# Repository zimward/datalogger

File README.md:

4-20mA dual channel Datalogger for long term averaging of in-field bus systems

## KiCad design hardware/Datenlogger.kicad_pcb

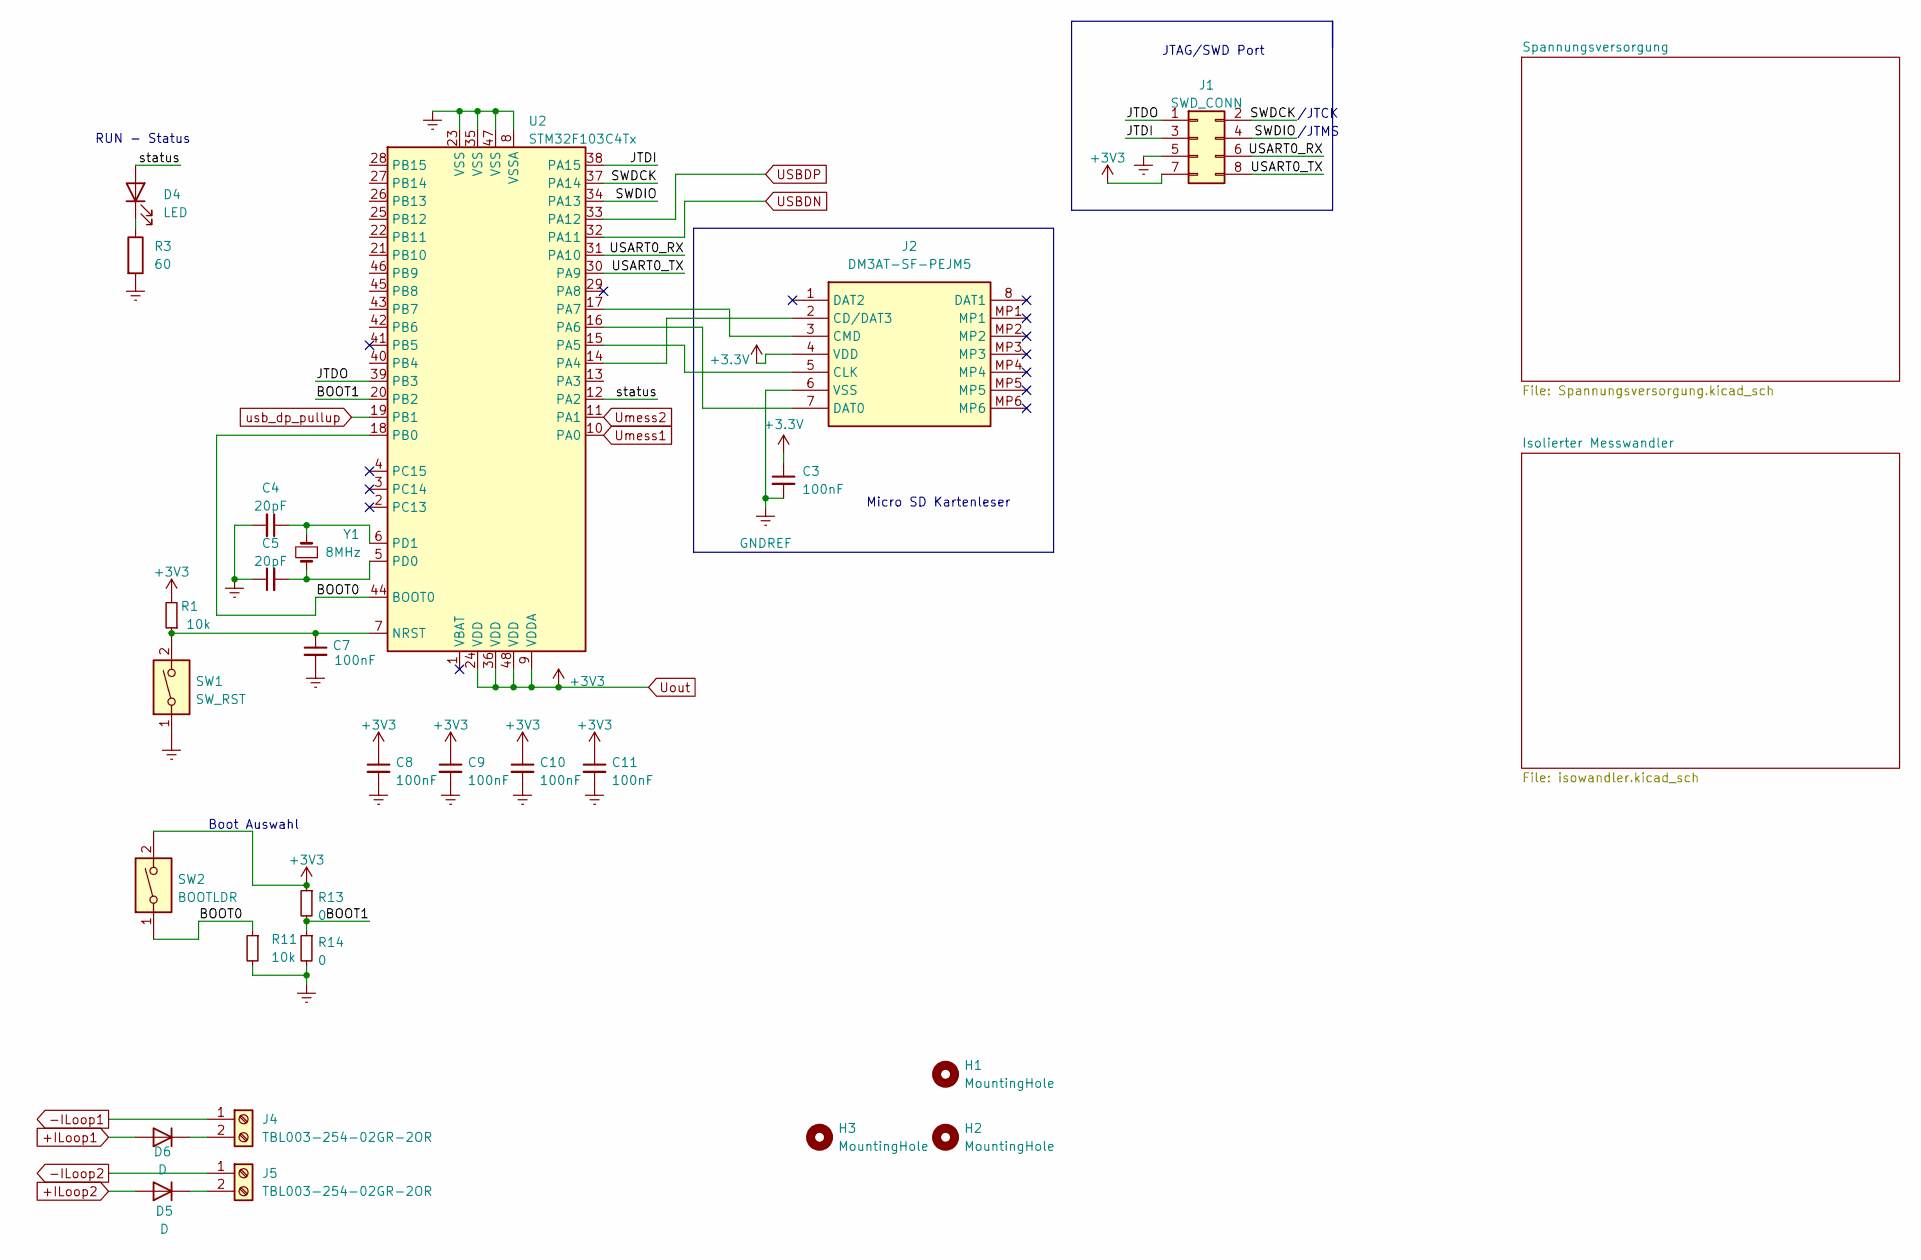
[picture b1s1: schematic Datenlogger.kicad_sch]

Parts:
C3, C7, C8, C9, C10, C11: 100nF; C_0805_2012Metric_Pad1.18x1.45mm_HandSolder
C4, C5: 20pF; C_0805_2012Metric_Pad1.18x1.45mm_HandSolder
D4: LED; LED_0805_2012Metric_Pad1.15x1.40mm_HandSolder
D5, D6: D; D_SOD-123
H1, H2, H3: MountingHole; MountingHole_3.2mm_M3_DIN965
J1: SWD_CONN; PinHeader_2x04_P2.54mm_Vertical
J2: DM3AT-SF-PEJM5; DM3ATSFPEJM5; Mouser Part Number 798-DM3AT-SF-PEJM5
J4, J5: TBL003-254-02GR-2OR; SHDR4W70P508X254_2X2_768X1380X1275P
R1, R11: 10k; R_0805_2012Metric_Pad1.20x1.40mm_HandSolder
R3: 60; R_0805_2012Metric_Pad1.20x1.40mm_HandSolder
R13, R14: 0; R_0805_2012Metric_Pad1.20x1.40mm_HandSolder
SW1: SW_RST; SW_DIP_SPSTx01_Slide_6.7x4.1mm_W7.62mm_P2.54mm_LowProfile
SW2: BOOTLDR; SW_DIP_SPSTx01_Slide_6.7x4.1mm_W7.62mm_P2.54mm_LowProfile
U2: STM32F103C4Tx; LQFP-48_7x7mm_P0.5mm
Y1: 8MHz; Crystal_SMD_HC49-SD

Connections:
+ILoop1: D6.2 (A); also elsewhere on the board
+ILoop2: D5.2 (A); also elsewhere on the board
-ILoop1: J4.1; also elsewhere on the board
-ILoop2: J5.1; also elsewhere on the board
/BOOT0: R11.1, SW2.1, U2.18 (PB0), U2.44 (BOOT0)
/BOOT1: R13.2, R14.1, U2.20 (PB2)
/JTDI: J1.3, U2.38 (PA15)
/JTDO: J1.1, U2.39 (PB3)
/SWDCK: J1.2, U2.37 (PA14)
/SWDIO: J1.4, U2.34 (PA13)
/USART0_RX: J1.6, U2.31 (PA10)
/USART0_TX: J1.8, U2.30 (PA9)
/status: D4.2 (A), U2.12 (PA2)
GNDREF: C3.2, C4.2, C5.1, C7.2, C8.2, C9.2, C10.2, C11.2, J1.5, J2.6 (VSS), R3.2, R11.2, R14.2, SW1.1, U2.8 (VSSA), U2.23 (VSS), U2.35 (VSS), U2.47 (VSS); also elsewhere on the board
unnamed: D4.1 (K), R3.1
unnamed: D5.1 (K), J5.2
unnamed: D6.1 (K), J4.2
unnamed: J2.2 (CD/DAT3), U2.14 (PA4)
unnamed: J2.5 (CLK), U2.15 (PA5)
unnamed: J2.3 (CMD), U2.17 (PA7)
unnamed: J2.7 (DAT0), U2.16 (PA6)
unnamed: C7.1, R1.1, SW1.2, U2.7 (NRST)
unnamed: C5.2, U2.5 (PD0), Y1.1
unnamed: C4.1, U2.6 (PD1), Y1.2
USBDN: U2.32 (PA11); also elsewhere on the board
USBDP: U2.33 (PA12); also elsewhere on the board
Umess1: U2.10 (PA0); also elsewhere on the board
Umess2: U2.11 (PA1); also elsewhere on the board
Uout: C3.1, C8.1, C9.1, C10.1, C11.1, J1.7, J2.4 (VDD), R1.2, R13.1, SW2.2, U2.9 (VDDA), U2.24 (VDD), U2.36 (VDD), U2.48 (VDD); also elsewhere on the board
usb_dp_pullup: U2.19 (PB1); also elsewhere on the board

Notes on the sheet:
JTAG/SWD Port
Micro SD Kartenleser
/JTMS
/JTCK
Boot Auswahl
RUN - Status

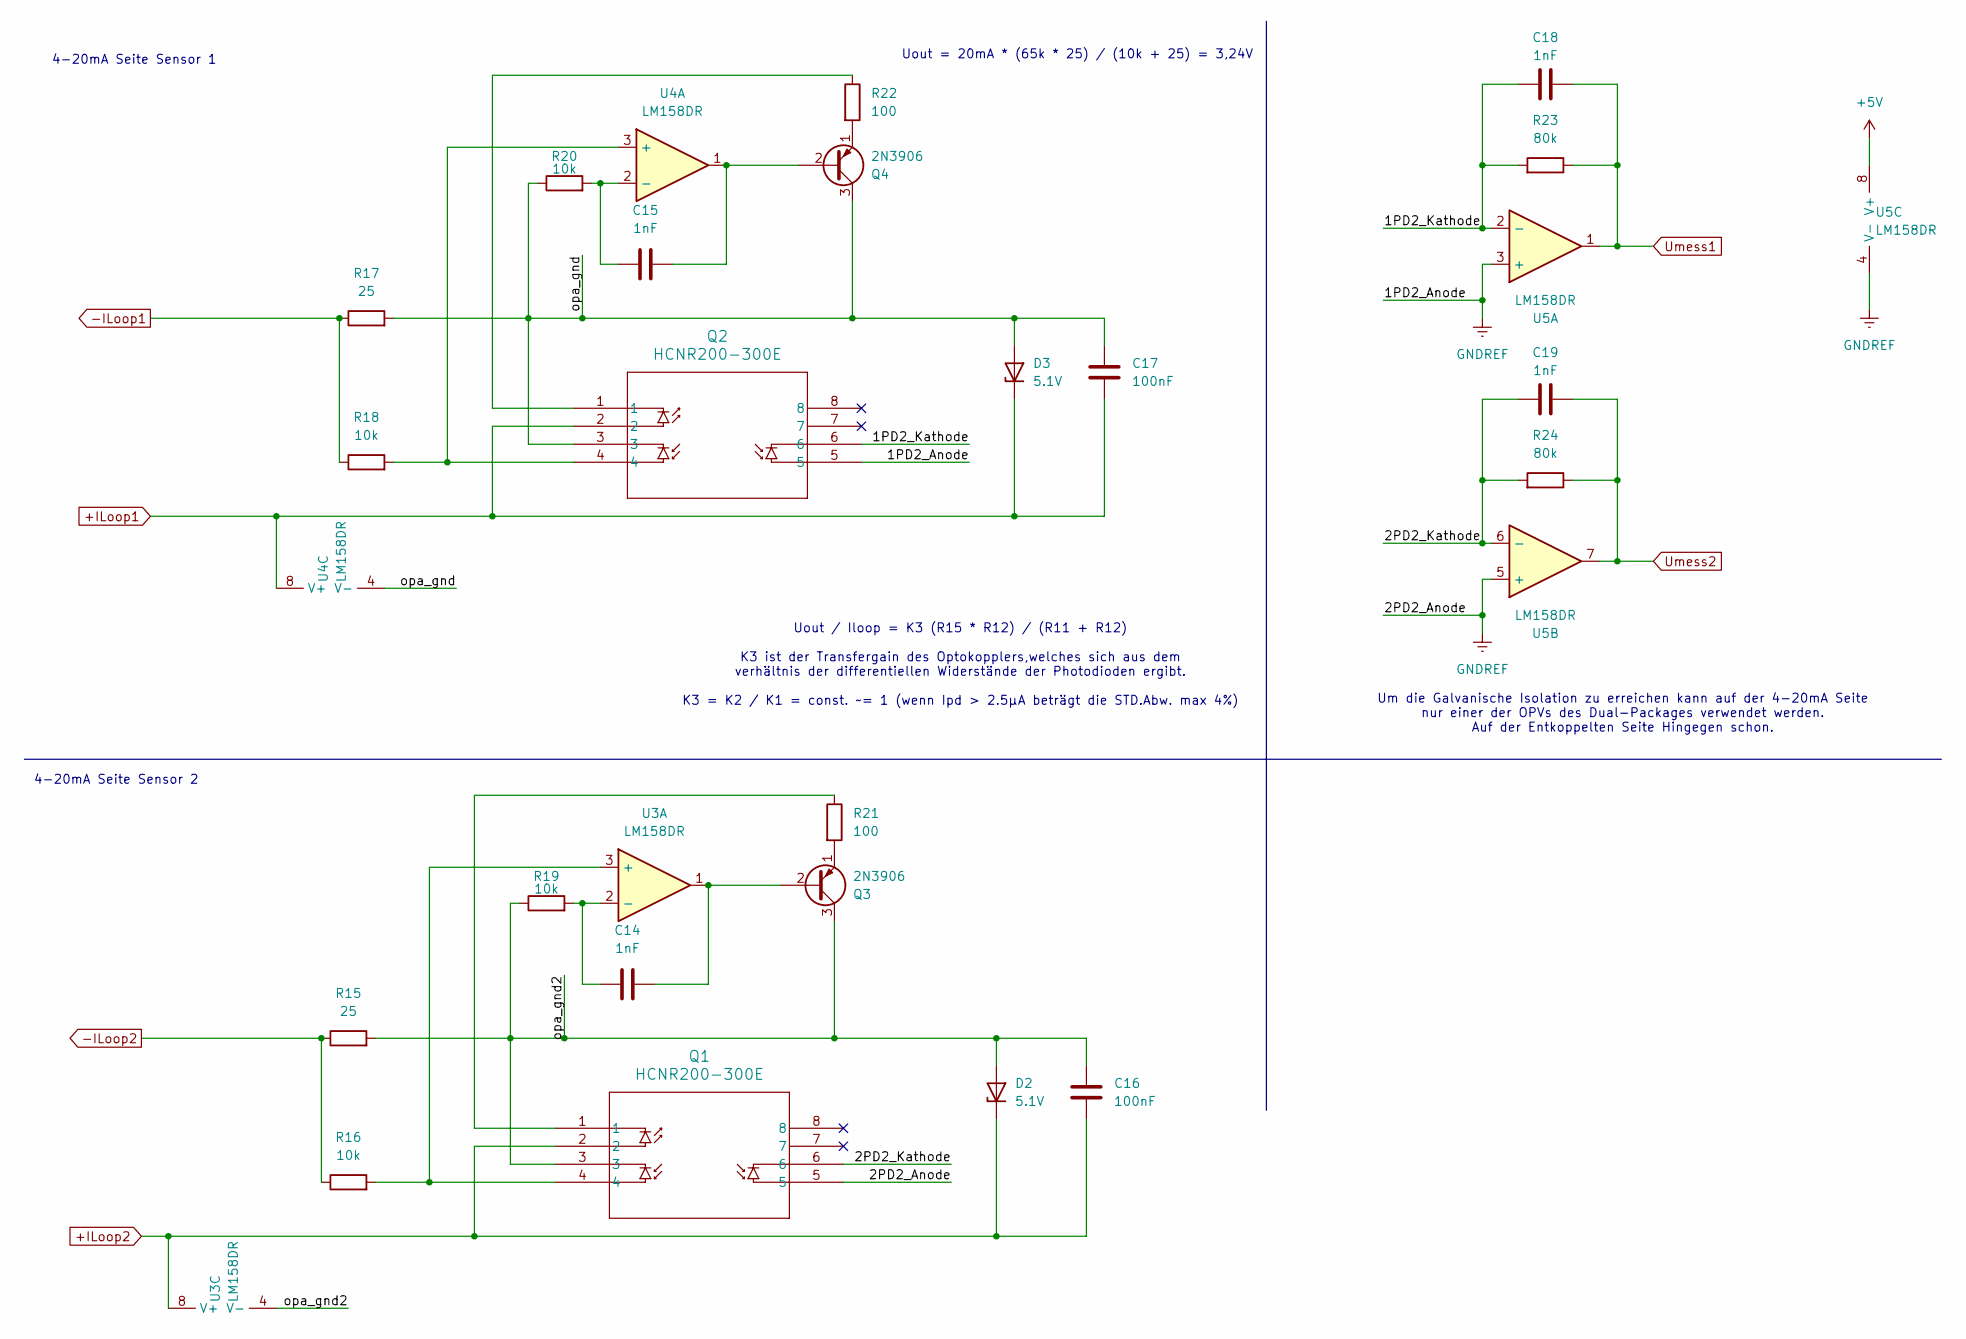
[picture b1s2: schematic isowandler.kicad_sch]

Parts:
C14, C15, C18, C19: 1nF; C_0805_2012Metric_Pad1.18x1.45mm_HandSolder
C16, C17: 100nF; C_0805_2012Metric_Pad1.18x1.45mm_HandSolder
D2, D3: 5.1V; D_SOD-123
Q1, Q2: HCNR200-300E
Q3, Q4: 2N3906; TO-92_Inline_Wide
R15, R17: 25; R_0805_2012Metric_Pad1.20x1.40mm_HandSolder
R16, R18, R19, R20: 10k; R_0805_2012Metric_Pad1.20x1.40mm_HandSolder
R21, R22: 100; R_0805_2012Metric_Pad1.20x1.40mm_HandSolder
R23, R24: 80k; R_0805_2012Metric_Pad1.20x1.40mm_HandSolder
U3, U4, U5: LM158DR; SOP-8_3.76x4.96mm_P1.27mm

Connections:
+5V: U5.8 (V+)
+ILoop1: C17.2, D3.1 (K), Q2.2, U4.8 (V+); also elsewhere on the board
+ILoop2: C16.2, D2.1 (K), Q1.2, U3.8 (V+); also elsewhere on the board
-ILoop1: R17.1, R18.1; also elsewhere on the board
-ILoop2: R15.1, R16.1; also elsewhere on the board
/Isolierter Messwandler/1PD2_Kathode: C18.1, Q2.6, R23.2, U5.2 (-)
/Isolierter Messwandler/2PD2_Kathode: C19.1, Q1.6, R24.2, U5.6 (-)
/Isolierter Messwandler/opa_gnd: C17.1, D3.2 (A), Q2.3, Q4.3 (C), R17.2, R20.1, U4.4 (V-)
/Isolierter Messwandler/opa_gnd2: C16.1, D2.2 (A), Q1.3, Q3.3 (C), R15.2, R19.1, U3.4 (V-)
GNDREF: Q1.5, Q2.5, U5.3 (+), U5.4 (V-), U5.5 (+); also elsewhere on the board
unnamed: Q1.1, R21.1
unnamed: Q2.1, R22.1
unnamed: C14.2, Q3.2 (B), U3.1
unnamed: Q3.1 (E), R21.2
unnamed: C15.2, Q4.2 (B), U4.1
unnamed: Q4.1 (E), R22.2
unnamed: Q1.4, R16.2, U3.3 (+)
unnamed: C14.1, R19.2, U3.2 (-)
unnamed: Q2.4, R18.2, U4.3 (+)
unnamed: C15.1, R20.2, U4.2 (-)
Umess1: C18.2, R23.1, U5.1; also elsewhere on the board
Umess2: C19.2, R24.1, U5.7; also elsewhere on the board

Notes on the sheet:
Um die Galvanische Isolation zu erreichen kann auf der 4-20mA Seite nur einer der OPVs des Dual-Packages verwendet werden. Auf der Entkoppelten Seite Hingegen schon.
Uout = 20mA * (65k * 25) / (10k + 25) = 3,24V
4-20mA Seite Sensor 1
Uout / Iloop = K3 (R15 * R12) / (R11 + R12) K3 ist der Transfergain des Optokopplers,welches sich aus dem verhältnis der differentiellen Widerstände der Photodioden ergibt. K3 = K2 / K1 = const. ~= 1 (wenn Ipd > 2.5µA beträgt die STD.Abw. max 4%)
4-20mA Seite Sensor 2

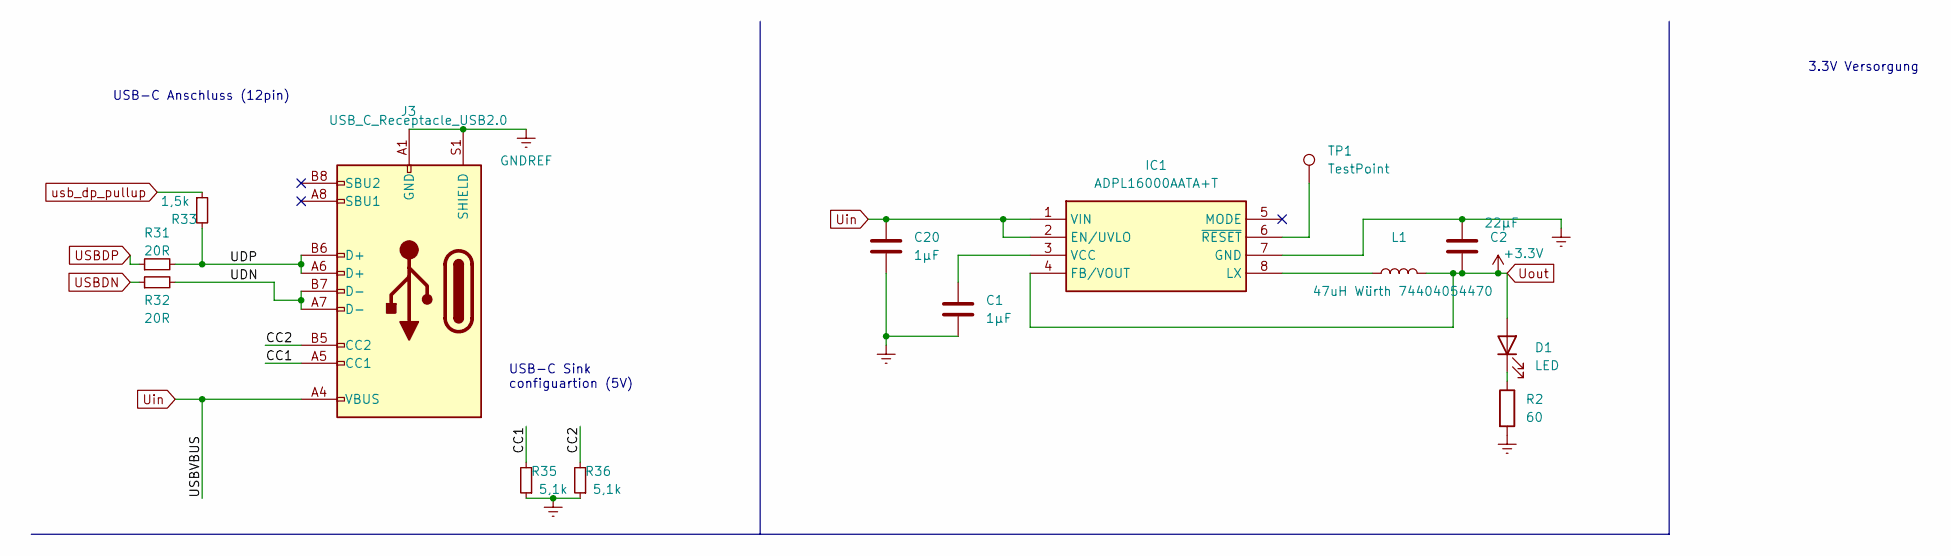
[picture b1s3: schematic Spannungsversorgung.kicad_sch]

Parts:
C1: 1µF; C_0805_2012Metric_Pad1.18x1.45mm_HandSolder
C2: 22µF; C_0805_2012Metric_Pad1.18x1.45mm_HandSolder
C20: 1µF; C_0805_2012Metric
D1: LED; LED_0805_2012Metric_Pad1.15x1.40mm_HandSolder
IC1: ADPL16000AATA+T; ADPL16000AATAT; Mouser Part Number 700-ADPL16000AATA+T
J3: USB_C_Receptacle_USB2.0; USB_C_Receptacle_Palconn_UTC16-G
L1: 47uH Würth 74404054470; 74404054470
R2: 60; R_0805_2012Metric_Pad1.20x1.40mm_HandSolder
R31, R32: 20R; R_0805_2012Metric_Pad1.20x1.40mm_HandSolder
R33: 1,5k; R_0805_2012Metric_Pad1.20x1.40mm_HandSolder
R35, R36: 5,1k; R_0805_2012Metric_Pad1.20x1.40mm_HandSolder
TP1: TestPoint; TestPoint_Pad_1.5x1.5mm

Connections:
/Spannungsversorgung/CC1: J3.A5 (CC1), R35.2
/Spannungsversorgung/CC2: J3.B5 (CC2), R36.2
/Spannungsversorgung/UDN: J3.A7 (D-), J3.B7 (D-), R32.2
/Spannungsversorgung/UDP: J3.A6 (D+), J3.B6 (D+), R31.2, R33.2
GNDREF: C1.2, C2.1, C20.2, IC1.7 (GND), J3.A1 (GND), J3.A12 (GND), J3.B1 (GND), J3.B12 (GND), J3.S1 (SHIELD), R2.2, R35.1, R36.1; also elsewhere on the board
unnamed: D1.1 (K), R2.1
unnamed: IC1.8 (LX), L1.1
unnamed: C1.1, IC1.3 (VCC)
unnamed: IC1.6 (~RESET), TP1.1
USBDN: R32.1; also elsewhere on the board
USBDP: R31.1; also elsewhere on the board
Uin: C20.1, IC1.1 (VIN), IC1.2 (EN/UVLO), J3.A4 (VBUS), J3.A9 (VBUS), J3.B4 (VBUS), J3.B9 (VBUS)
Uout: C2.2, D1.2 (A), IC1.4 (FB/VOUT), L1.2; also elsewhere on the board
usb_dp_pullup: R33.1; also elsewhere on the board

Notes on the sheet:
USB-C Sink configuartion (5V)
3.3V Versorgung
USB-C Anschluss (12pin)

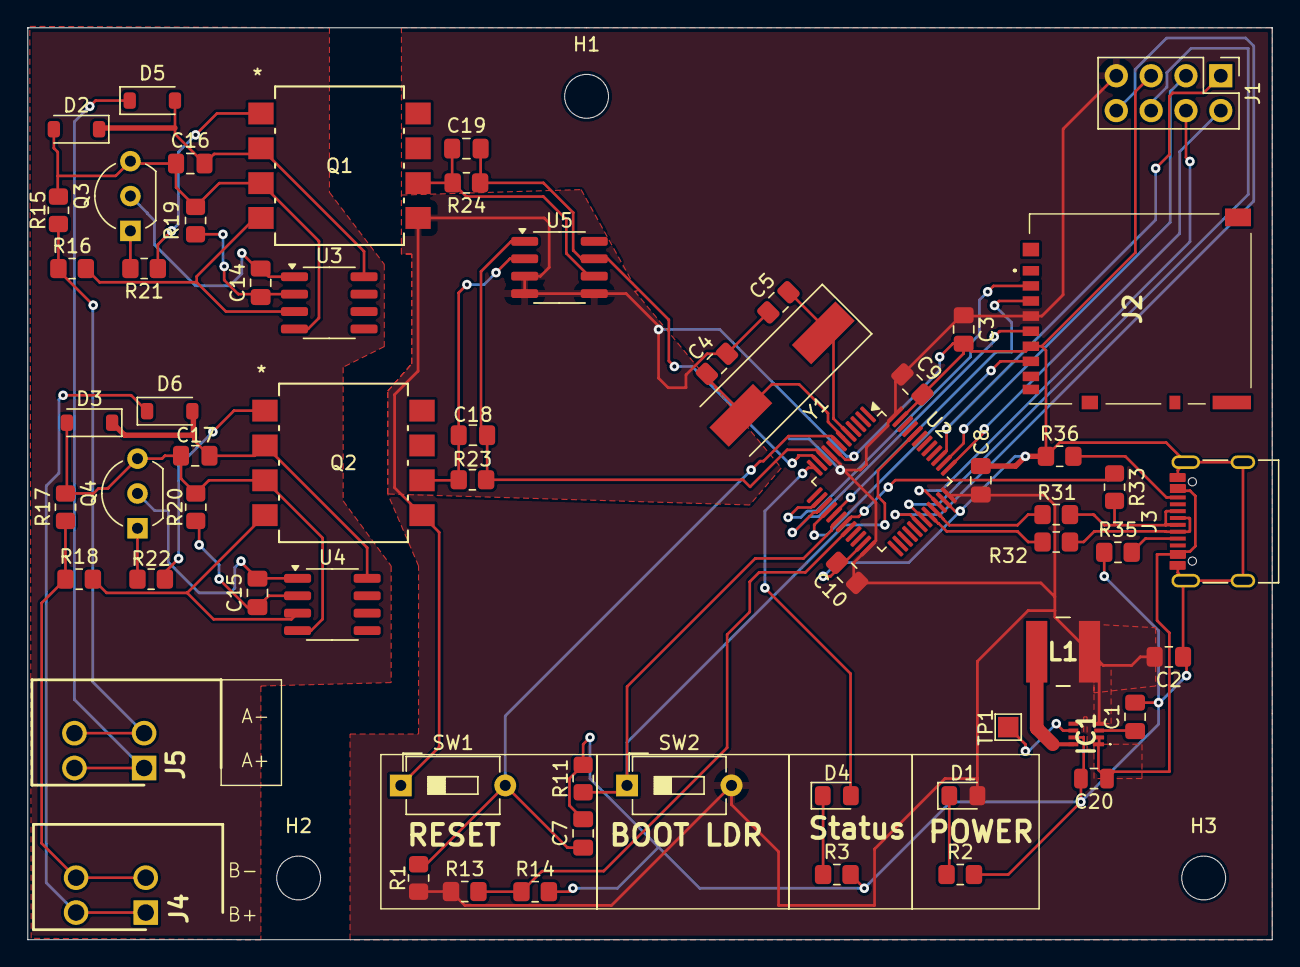
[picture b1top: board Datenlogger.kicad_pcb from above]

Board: 2 copper layers, 90.8 x 66.5 mm, 66 parts (1 on the bottom side), 53 nets.

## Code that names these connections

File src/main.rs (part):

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use sdcard::{config_error, sderror, FakeTimeSource};
use stm32f1xx_hal::adc::{Adc, SampleTime, SetChannels};
use stm32f1xx_hal::dma::Half;
use stm32f1xx_hal::gpio::{Analog, PA0, PA1};
use stm32f1xx_hal::pac::{ADC1, NVIC, TIM3};

use stm32f1xx_hal::spi::Spi;
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/*
#######################
pin  funktion
PB1  usb dp pin pullup
PA0  messkanal B
PA1  messkanal A
PA2  status LED
PB0 start/stop -- in dokumentation nach remap möglichkeit schauen.

#######################
*/
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
    //ADC dma config
    let mut adc = {
        struct AdcPins(PA0<Analog>, PA1<Analog>);
        impl SetChannels<AdcPins> for Adc<ADC1> {
            fn set_sequence(&mut self) {
                //first channel A then B, but doesn't really matter
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            }
        }

        let channelB = gpioa.pa0.into_analog(&mut gpioa.crl);
        let channelA = gpioa.pa1.into_analog(&mut gpioa.crl);

        let mut adc = Adc::adc1(dp.ADC1, clocks);
        //slowest sampling time should be sufficient
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    let mut gpiob = dp.GPIOB.split();
    let spi = {
        let pins = (
            gpioa.pa5.into_alternate_push_pull(&mut gpioa.crl),
            gpioa.pa6.into_pull_up_input(&mut gpioa.crl),
            gpioa.pa7.into_alternate_push_pull(&mut gpioa.crl),
        );
        let spi_mode = Mode {
            polarity: embedded_hal::spi::Polarity::IdleLow,
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        spi
    };

    let btn = gpiob.pb0.into_floating_input(&mut gpiob.crl);

    let mut led = {
        // let led_pin = gpioa.pa2.into_alternate_push_pull(&mut gpioa.crl);
        let mut led_pin = gpioa.pa2.into_push_pull_output(&mut gpioa.crl);
        // let mut pwm = Timer::new(dp.TIM2, &clocks).pwm_hz::<Tim2NoRemap, _, _>(
        //     led_pin,
        //     &mut afio.mapr,
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
    let delay = cp.SYST.delay(&clocks);

    let sdcard = SdCard::new(spi, gpioa.pa4.into_push_pull_output(&mut gpioa.crl), delay);
    let mut volume_mgr = VolumeManager::new(sdcard, FakeTimeSource::new());
    let vol0 = volume_mgr
        .open_volume(VolumeIdx(0))
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
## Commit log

2025-03-06 initial dev env
2025-03-06 update config
2025-03-06 add panic handler
2025-03-12 add pin defs
2025-03-12 fix linker error
2025-03-12 inital draft for led pwm control
2025-03-13 inital LED control; ADC with DMA
2025-03-17 implemented averaging of adc samples
2025-03-18 initial spi init
2025-03-19 initial config setup
2025-04-11 Datahandling logic
2025-04-11 implemented writing values to sdcard
2025-04-11 emit different error code for malformed config
2025-04-14 fix sdcard pins, todo: adc processing
2025-04-22 fix logic bugs
2025-04-22 add gdb
2025-04-22 increase SPI clock to 8MHz, as sdcard times out otherwise
2025-04-22 fix millis timer; implement start/stop logic
2025-04-22 cleanup debug logic
2026-04-29 add hardware design
2026-04-29 add license
2026-04-29 actually update readme to be correct
